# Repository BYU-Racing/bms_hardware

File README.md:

# BYU Racing 2027 BMS Project

This repo contains all relevant PCB files and explanations relating to the team's custom solution for a Battery Management System (BMS)

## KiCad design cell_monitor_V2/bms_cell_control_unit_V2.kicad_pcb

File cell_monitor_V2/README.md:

# BMS Cell Monitor V2 Files
This folder contains the KiCad project files for the BMS Cell Monitor V2.

PCB handoff from Rugby 11/10/2026 ☠️🌹⛓️

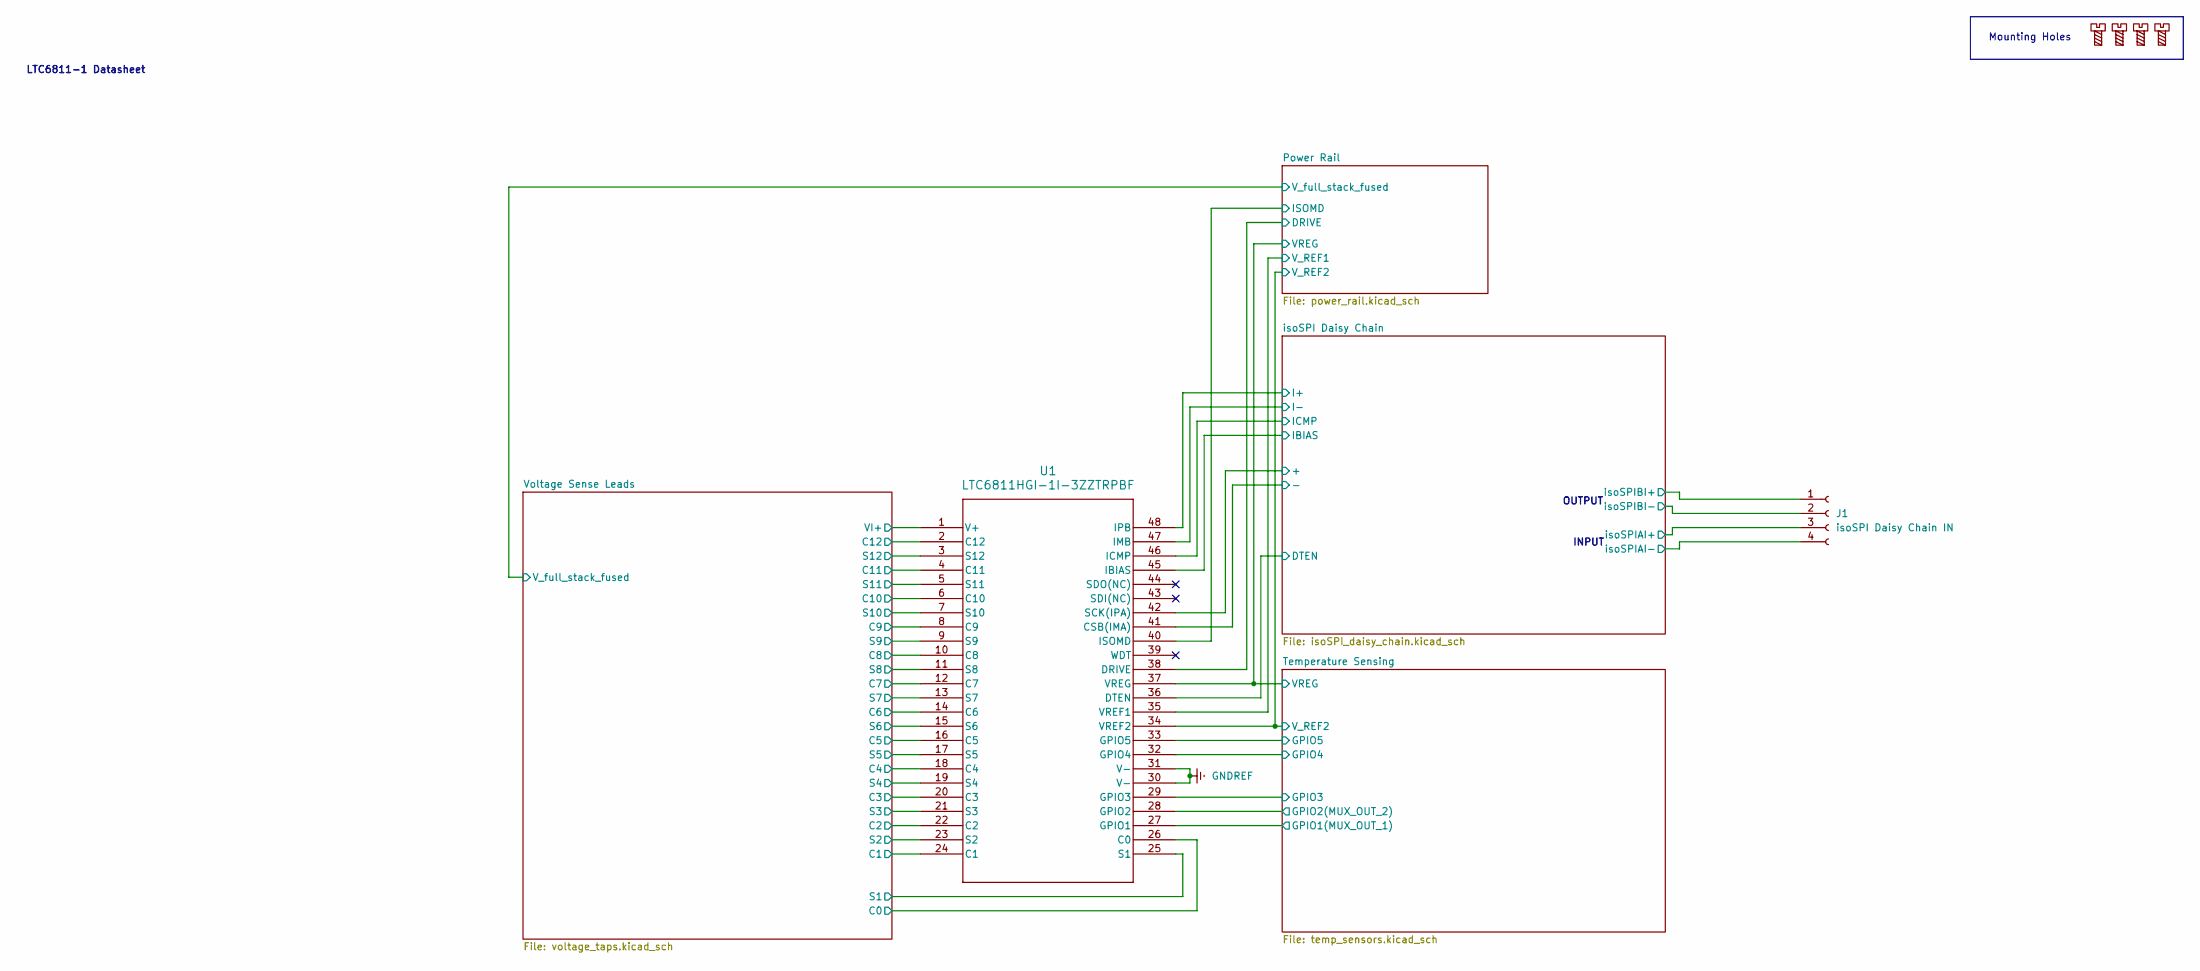
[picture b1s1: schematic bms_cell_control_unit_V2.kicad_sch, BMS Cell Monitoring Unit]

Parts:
H13, H14, H15, H16: MountingScrew; MountingHole_4mm
J1: isoSPI Daisy Chain IN; Molex_Micro-Fit_3.0_43650-0400_1x04_P3.00mm_Horizontal
U1: LTC6811HGI-1I-3ZZTRPBF; 05-08-1887_ADI

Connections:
/Power Rail/DRIVE: U1.38 (DRIVE); also elsewhere on the board
/Power Rail/VREG: U1.37 (VREG), U1.40 (ISOMD); also elsewhere on the board
/Power Rail/V_REF1: U1.35 (VREF1); also elsewhere on the board
/Power Rail/V_REF2: U1.34 (VREF2); also elsewhere on the board
/Temperature Sensing/GPIO1(MUX_OUT_1): U1.27 (GPIO1); also elsewhere on the board
/Temperature Sensing/GPIO2(MUX_OUT_2): U1.28 (GPIO2); also elsewhere on the board
/Temperature Sensing/GPIO3: U1.29 (GPIO3); also elsewhere on the board
/Temperature Sensing/GPIO4: U1.32 (GPIO4); also elsewhere on the board
/Temperature Sensing/GPIO5: U1.33 (GPIO5); also elsewhere on the board
/Voltage Sense Leads/C0: U1.26 (C0); also elsewhere on the board
/Voltage Sense Leads/C1: U1.24 (C1); also elsewhere on the board
/Voltage Sense Leads/C2: U1.22 (C2); also elsewhere on the board
/Voltage Sense Leads/C3: U1.20 (C3); also elsewhere on the board
/Voltage Sense Leads/C4: U1.18 (C4); also elsewhere on the board
/Voltage Sense Leads/C5: U1.16 (C5); also elsewhere on the board
/Voltage Sense Leads/C6: U1.14 (C6); also elsewhere on the board
/Voltage Sense Leads/C7: U1.12 (C7); also elsewhere on the board
/Voltage Sense Leads/C8: U1.10 (C8); also elsewhere on the board
/Voltage Sense Leads/C9: U1.8 (C9); also elsewhere on the board
/Voltage Sense Leads/C10: U1.6 (C10); also elsewhere on the board
/Voltage Sense Leads/C11: U1.4 (C11); also elsewhere on the board
/Voltage Sense Leads/C12: U1.2 (C12); also elsewhere on the board
/Voltage Sense Leads/S1: U1.25 (S1); also elsewhere on the board
/Voltage Sense Leads/S2: U1.23 (S2); also elsewhere on the board
/Voltage Sense Leads/S3: U1.21 (S3); also elsewhere on the board
/Voltage Sense Leads/S4: U1.19 (S4); also elsewhere on the board
/Voltage Sense Leads/S5: U1.17 (S5); also elsewhere on the board
/Voltage Sense Leads/S6: U1.15 (S6); also elsewhere on the board
/Voltage Sense Leads/S7: U1.13 (S7); also elsewhere on the board
/Voltage Sense Leads/S8: U1.11 (S8); also elsewhere on the board
/Voltage Sense Leads/S9: U1.9 (S9); also elsewhere on the board
/Voltage Sense Leads/S10: U1.7 (S10); also elsewhere on the board
/Voltage Sense Leads/S11: U1.5 (S11); also elsewhere on the board
/Voltage Sense Leads/S12: U1.3 (S12); also elsewhere on the board
/Voltage Sense Leads/VI+: U1.1 (V+); also elsewhere on the board
/isoSPI Daisy Chain/+: U1.42 (SCK(IPA)); also elsewhere on the board
/isoSPI Daisy Chain/-: U1.41 (CSB(IMA)); also elsewhere on the board
/isoSPI Daisy Chain/I+: U1.48 (IPB); also elsewhere on the board
/isoSPI Daisy Chain/I-: U1.47 (IMB); also elsewhere on the board
/isoSPI Daisy Chain/IBIAS: U1.45 (IBIAS); also elsewhere on the board
/isoSPI Daisy Chain/ICMP: U1.46 (ICMP); also elsewhere on the board
/isoSPI Daisy Chain/isoSPIAI+: J1.3; also elsewhere on the board
/isoSPI Daisy Chain/isoSPIAI-: J1.4; also elsewhere on the board
/isoSPI Daisy Chain/isoSPIBI+: J1.1; also elsewhere on the board
/isoSPI Daisy Chain/isoSPIBI-: J1.2; also elsewhere on the board
GNDREF: U1.30 (V-), U1.31 (V-), U1.36 (DTEN); also elsewhere on the board

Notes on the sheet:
OUTPUT
INPUT
LTC6811-1 Datasheet
Mounting Holes

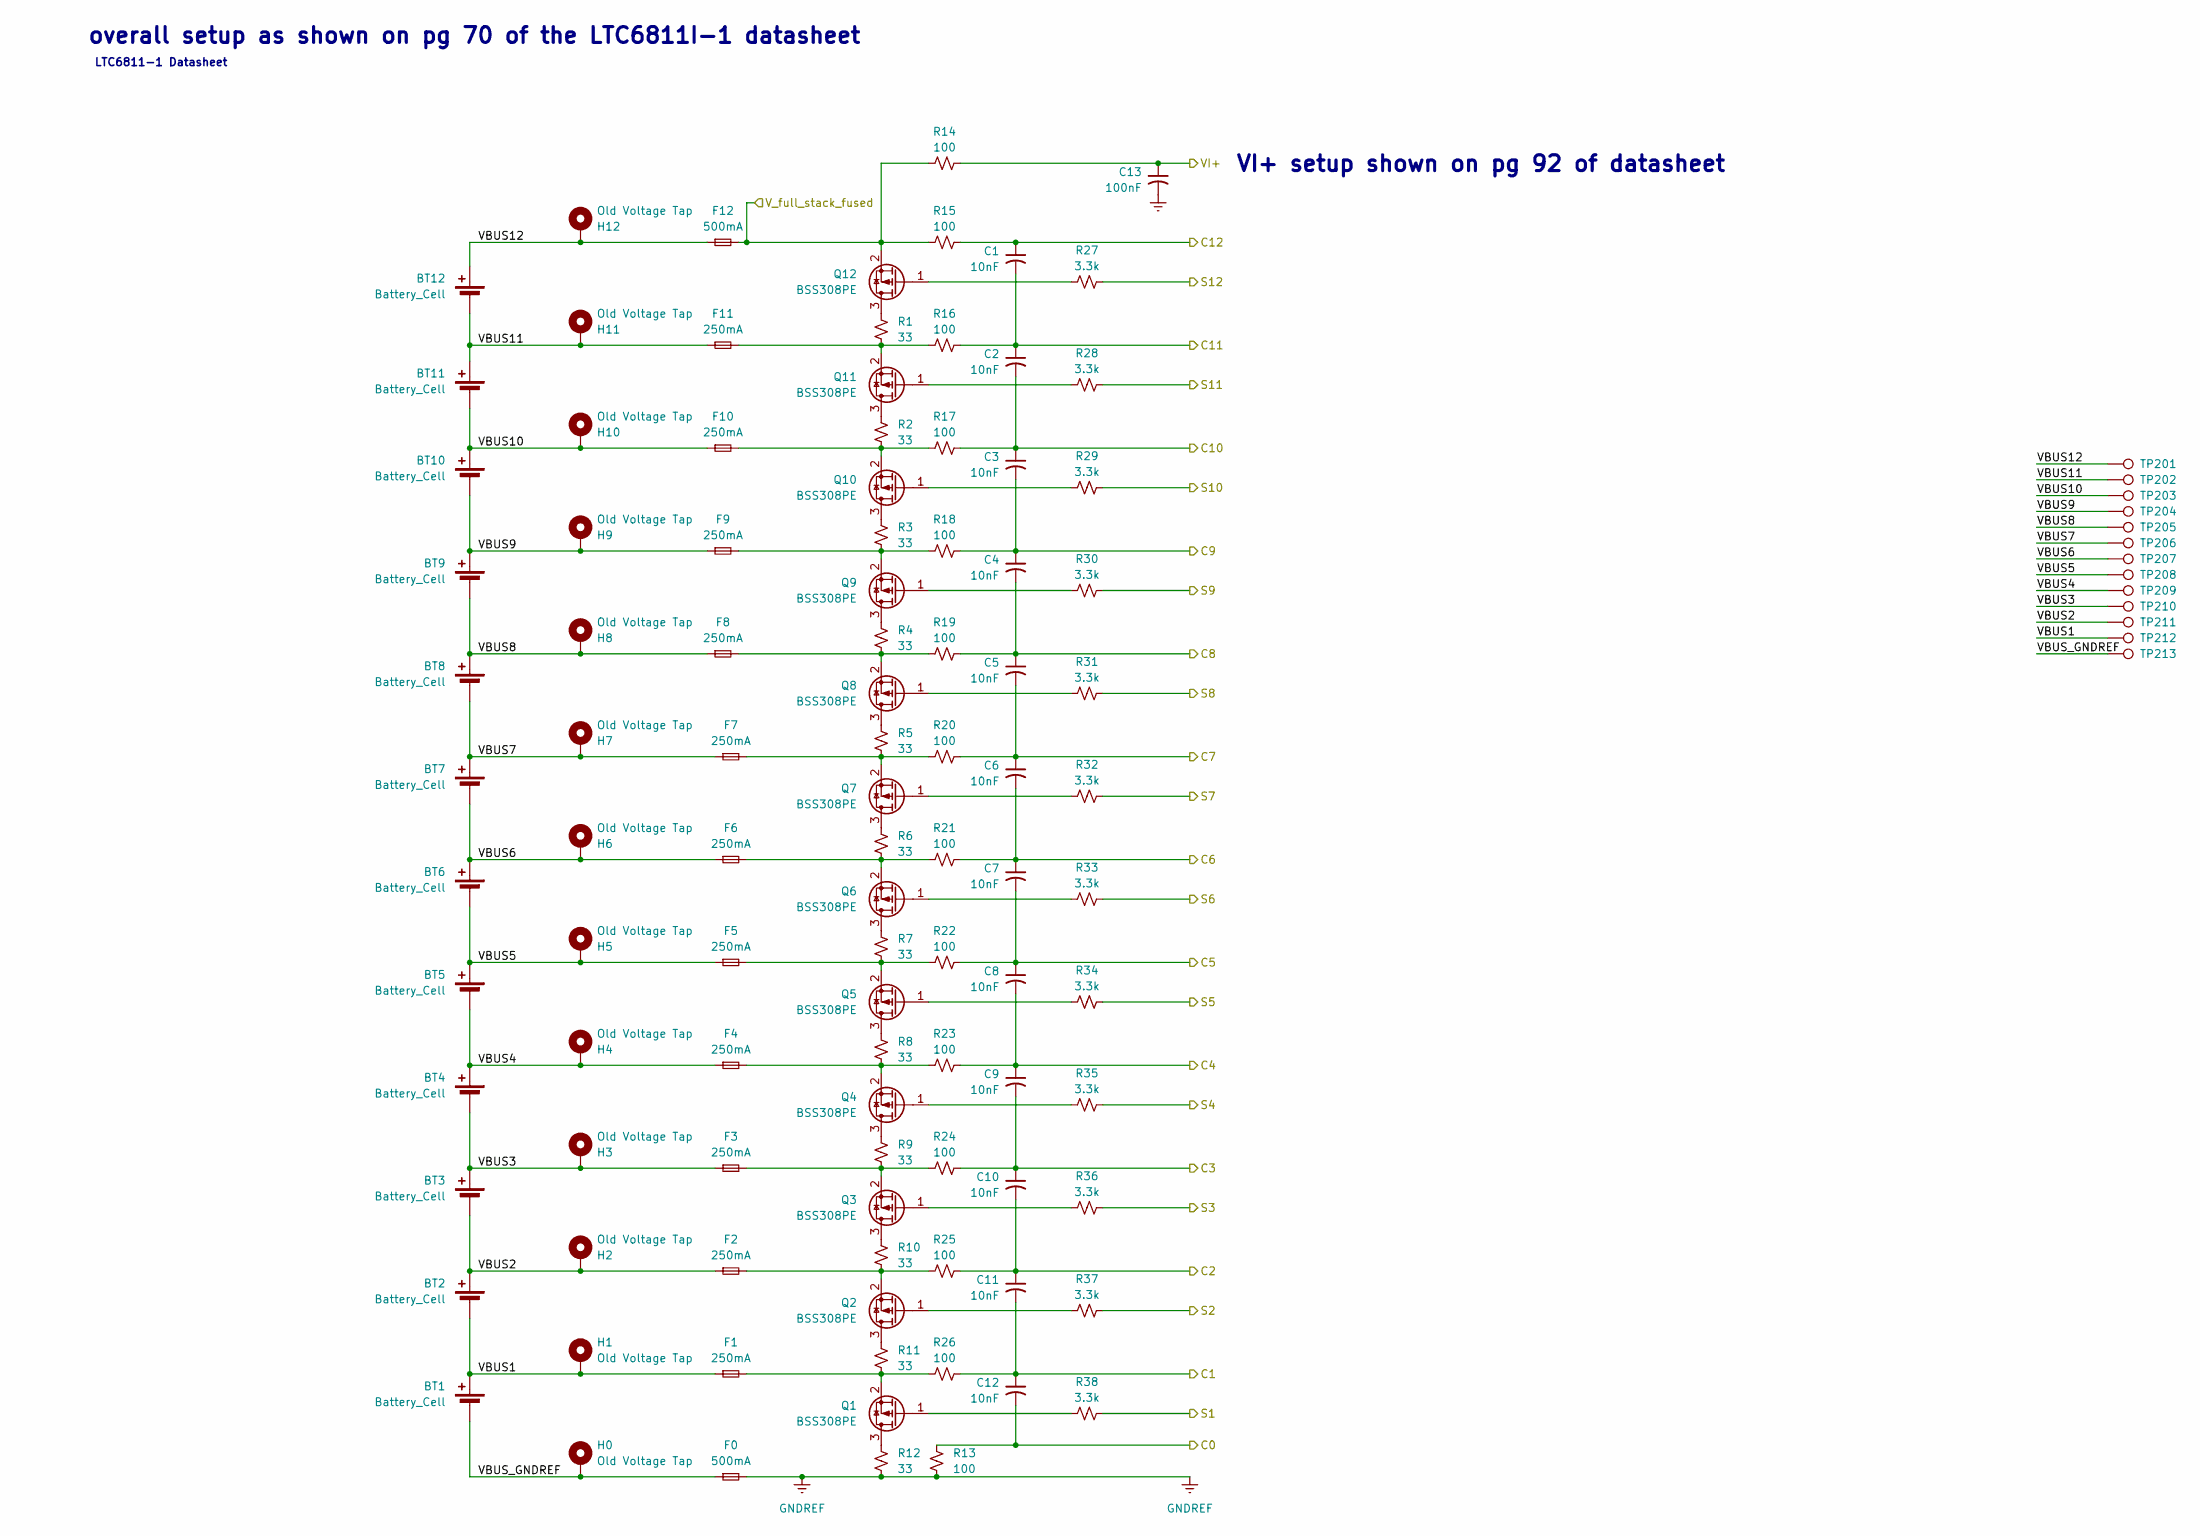
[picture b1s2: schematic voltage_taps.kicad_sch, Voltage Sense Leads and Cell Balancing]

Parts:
BT1, BT2, BT3, BT4, BT5, BT6, BT7, BT8, BT9, BT10, BT11, BT12: Battery_Cell
C1, C2, C3, C4, C5, C6, C7, C8, C9, C10, C11, C12: 10nF; C_0603_1608Metric_Pad1.08x0.95mm_HandSolder
C13: 100nF; C_0805_2012Metric_Pad1.18x1.45mm_HandSolder
F0, F12: 500mA; Littelfuse_01550900M_Fuse_Blok_Cartridge
F1, F2, F3, F4, F5, F6, F7, F8, F9, F10, F11: 250mA; Littelfuse_01550900M_Fuse_Blok_Cartridge
H0, H1, H2, H3, H4, H5, H6, H7, H8, H9, H10, H11, H12: Old Voltage Tap; Votage_taps
Q1, Q2, Q3, Q4, Q5, Q6, Q7, Q8, Q9, Q10, Q11, Q12: BSS308PE; SOT-23_Handsoldering
R1, R2, R3, R4, R5, R6, R7, R8, R9, R10, R11, R12: 33; Balance_Resistor_Thermal_Pad_Updated
R13, R14, R15, R16, R17, R18, R19, R20, R21, R22, R23, R24, R25, R26: 100; R_0603_1608Metric_Pad0.98x0.95mm_HandSolder
R27, R28, R29, R30, R31, R32, R33, R34, R35, R36, R37, R38: 3.3k; R_0603_1608Metric_Pad0.98x0.95mm_HandSolder
TP201, TP202, TP203, TP204, TP205, TP206, TP207, TP208, TP209, TP210, TP211, TP212, TP213: TestPoint; TestPoint_Pad_D2.0mm

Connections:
/Power Rail/V_full_stack_fused: F12.2, Q12.2 (S), R14.2, R15.2; also elsewhere on the board
/Voltage Sense Leads/C0: C12.2, R13.1; also elsewhere on the board
/Voltage Sense Leads/C1: C11.2, C12.1, R26.1; also elsewhere on the board
/Voltage Sense Leads/C2: C10.2, C11.1, R25.1; also elsewhere on the board
/Voltage Sense Leads/C3: C9.2, C10.1, R24.1; also elsewhere on the board
/Voltage Sense Leads/C4: C8.2, C9.1, R23.1; also elsewhere on the board
/Voltage Sense Leads/C5: C7.2, C8.1, R22.1; also elsewhere on the board
/Voltage Sense Leads/C6: C6.2, C7.1, R21.1; also elsewhere on the board
/Voltage Sense Leads/C7: C5.2, C6.1, R20.1; also elsewhere on the board
/Voltage Sense Leads/C8: C4.2, C5.1, R19.1; also elsewhere on the board
/Voltage Sense Leads/C9: C3.2, C4.1, R18.1; also elsewhere on the board
/Voltage Sense Leads/C10: C2.2, C3.1, R17.1; also elsewhere on the board
/Voltage Sense Leads/C11: C1.2, C2.1, R16.1; also elsewhere on the board
/Voltage Sense Leads/C12: C1.1, R15.1; also elsewhere on the board
/Voltage Sense Leads/S1: R38.1; also elsewhere on the board
/Voltage Sense Leads/S2: R37.1; also elsewhere on the board
/Voltage Sense Leads/S3: R36.1; also elsewhere on the board
/Voltage Sense Leads/S4: R35.1; also elsewhere on the board
/Voltage Sense Leads/S5: R34.1; also elsewhere on the board
/Voltage Sense Leads/S6: R33.1; also elsewhere on the board
/Voltage Sense Leads/S7: R32.1; also elsewhere on the board
/Voltage Sense Leads/S8: R31.1; also elsewhere on the board
/Voltage Sense Leads/S9: R30.1; also elsewhere on the board
/Voltage Sense Leads/S10: R29.1; also elsewhere on the board
/Voltage Sense Leads/S11: R28.1; also elsewhere on the board
/Voltage Sense Leads/S12: R27.1; also elsewhere on the board
/Voltage Sense Leads/VBUS1: BT1.1 (+), BT2.2 (-), F1.1, H1.1 (1_1), TP212.1 (1_1)
/Voltage Sense Leads/VBUS2: BT2.1 (+), BT3.2 (-), F2.1, H2.1 (1_1), TP211.1 (1_1)
/Voltage Sense Leads/VBUS3: BT3.1 (+), BT4.2 (-), F3.1, H3.1 (1_1), TP210.1 (1_1)
/Voltage Sense Leads/VBUS4: BT4.1 (+), BT5.2 (-), F4.1, H4.1 (1_1), TP209.1 (1_1)
/Voltage Sense Leads/VBUS5: BT5.1 (+), BT6.2 (-), F5.1, H5.1 (1_1), TP208.1 (1_1)
/Voltage Sense Leads/VBUS6: BT6.1 (+), BT7.2 (-), F6.1, H6.1 (1_1), TP207.1 (1_1)
/Voltage Sense Leads/VBUS7: BT7.1 (+), BT8.2 (-), F7.1, H7.1 (1_1), TP206.1 (1_1)
/Voltage Sense Leads/VBUS8: BT8.1 (+), BT9.2 (-), F8.1, H8.1 (1_1), TP205.1 (1_1)
/Voltage Sense Leads/VBUS9: BT9.1 (+), BT10.2 (-), F9.1, H9.1 (1_1), TP204.1 (1_1)
/Voltage Sense Leads/VBUS10: BT10.1 (+), BT11.2 (-), F10.1, H10.1 (1_1), TP203.1 (1_1)
/Voltage Sense Leads/VBUS11: BT11.1 (+), BT12.2 (-), F11.1, H11.1 (1_1), TP202.1 (1_1)
/Voltage Sense Leads/VBUS12: BT12.1 (+), F12.1, H12.1 (1_1), TP201.1 (1_1)
/Voltage Sense Leads/VBUS_GNDREF: BT1.2 (-), F0.1, H0.1 (1_1), TP213.1 (1_1)
/Voltage Sense Leads/VI+: C13.1, R14.1; also elsewhere on the board
GNDREF: C13.2, F0.2, R12.2, R13.2; also elsewhere on the board
unnamed: Q1.3 (D), R12.1
unnamed: Q1.1 (G), R38.2
unnamed: F1.2, Q1.2 (S), R11.2, R26.2
unnamed: Q2.3 (D), R11.1
unnamed: Q2.1 (G), R37.2
unnamed: F2.2, Q2.2 (S), R10.2, R25.2
unnamed: Q3.3 (D), R10.1
unnamed: Q3.1 (G), R36.2
unnamed: F3.2, Q3.2 (S), R9.2, R24.2
unnamed: Q4.3 (D), R9.1
unnamed: Q4.1 (G), R35.2
unnamed: F4.2, Q4.2 (S), R8.2, R23.2
unnamed: Q5.3 (D), R8.1
unnamed: Q5.1 (G), R34.2
unnamed: F5.2, Q5.2 (S), R7.2, R22.2
unnamed: Q6.3 (D), R7.1
unnamed: Q6.1 (G), R33.2
unnamed: F6.2, Q6.2 (S), R6.2, R21.2
unnamed: Q7.3 (D), R6.1
unnamed: Q7.1 (G), R32.2
unnamed: F7.2, Q7.2 (S), R5.2, R20.2
unnamed: Q8.3 (D), R5.1
unnamed: Q8.1 (G), R31.2
unnamed: F8.2, Q8.2 (S), R4.2, R19.2
unnamed: Q9.3 (D), R4.1
unnamed: Q9.1 (G), R30.2
unnamed: F9.2, Q9.2 (S), R3.2, R18.2
unnamed: Q10.3 (D), R3.1
unnamed: Q10.1 (G), R29.2
unnamed: F10.2, Q10.2 (S), R2.2, R17.2
unnamed: Q11.3 (D), R2.1
unnamed: Q11.1 (G), R28.2
unnamed: F11.2, Q11.2 (S), R1.2, R16.2
unnamed: Q12.3 (D), R1.1
unnamed: Q12.1 (G), R27.2

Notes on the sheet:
LTC6811-1 Datasheet
VI+ setup shown on pg 92 of datasheet
overall setup as shown on pg 70 of the LTC6811I-1 datasheet

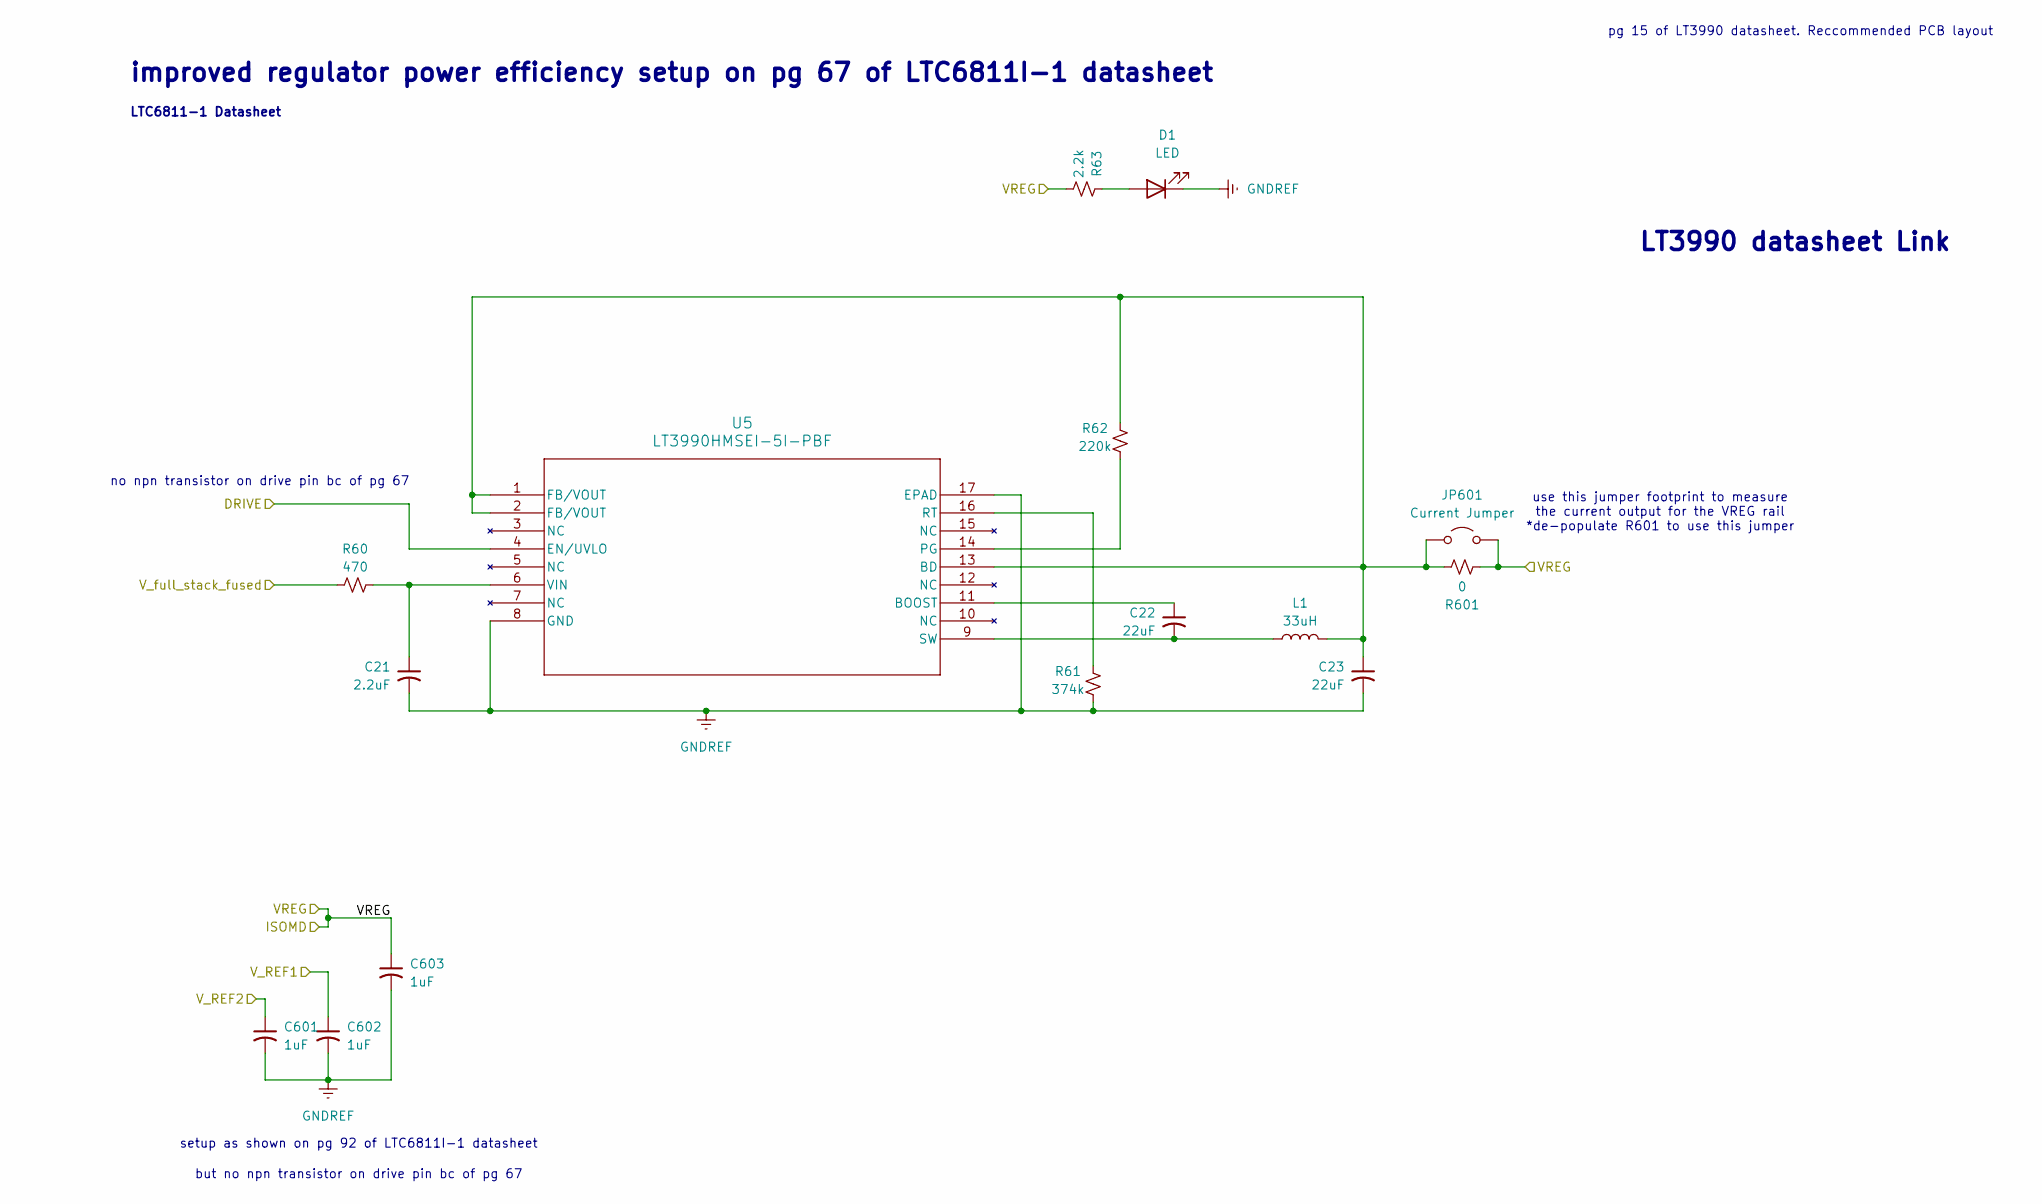
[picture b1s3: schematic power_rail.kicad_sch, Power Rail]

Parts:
C21: 2.2uF; C_1210_3225Metric_Pad1.33x2.70mm_HandSolder; DigiKey_Part_Number AC1210KKX7R0BB225
C22, C23: 22uF; C_0805_2012Metric_Pad1.18x1.45mm_HandSolder
C601, C602, C603: 1uF; C_0805_2012Metric_Pad1.18x1.45mm_HandSolder
D1: LED; R_0805_2012Metric_Pad1.20x1.40mm_HandSolder
JP601: Current Jumper; PinHeader_1x02_P2.54mm_Vertical
L1: 33uH; IND_LQH5BPH330MT0L; DigiKey_Part_Number LQH5BPH330MT0L
R60: 470; R_0805_2012Metric_Pad1.20x1.40mm_HandSolder
R61: 374k; R_0603_1608Metric_Pad0.98x0.95mm_HandSolder
R62: 220k; R_0603_1608Metric_Pad0.98x0.95mm_HandSolder
R63: 2.2k; R_0603_1608Metric_Pad0.98x0.95mm_HandSolder
R601: 0; R_0603_1608Metric_Pad0.98x0.95mm_HandSolder
U5: LT3990HMSEI-5I-PBF; MSOP-16-1EP_3x4.039mm_P0.5mm_EP1.651x2.845mm_ThermalVias

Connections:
/Power Rail/DRIVE: U5.4 (EN/UVLO); also elsewhere on the board
/Power Rail/VREG: C603.1, JP601.2 (B), R63.2, R601.2; also elsewhere on the board
/Power Rail/V_REF1: C602.1; also elsewhere on the board
/Power Rail/V_REF2: C601.1; also elsewhere on the board
/Power Rail/V_full_stack_fused: R60.2; also elsewhere on the board
GNDREF: C21.2, C23.2, C601.2, C602.2, C603.2, D1.1 (K), R61.2, U5.8 (GND), U5.17 (EPAD); also elsewhere on the board
unnamed: D1.2 (A), R63.1
unnamed: C23.1, JP601.1 (A), L1.2, R62.1, R601.1, U5.1 (FB/VOUT), U5.2 (FB/VOUT), U5.13 (BD)
unnamed: C22.1, U5.11 (BOOST)
unnamed: R62.2, U5.14 (PG)
unnamed: R61.1, U5.16 (RT)
unnamed: C22.2, L1.1, U5.9 (SW)
unnamed: C21.1, R60.1, U5.6 (VIN)

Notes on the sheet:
setup as shown on pg 92 of LTC6811I-1 datasheet
no npn transistor on drive pin bc of pg 67
LTC6811-1 Datasheet
pg 15 of LT3990 datasheet. Reccommended PCB layout
improved regulator power efficiency setup on pg 67 of LTC6811I-1 datasheet
but no npn transistor on drive pin bc of pg 67
LT3990 datasheet Link
use this jumper footprint to measure the current output for the VREG rail *de-populate R601 to use this jumper

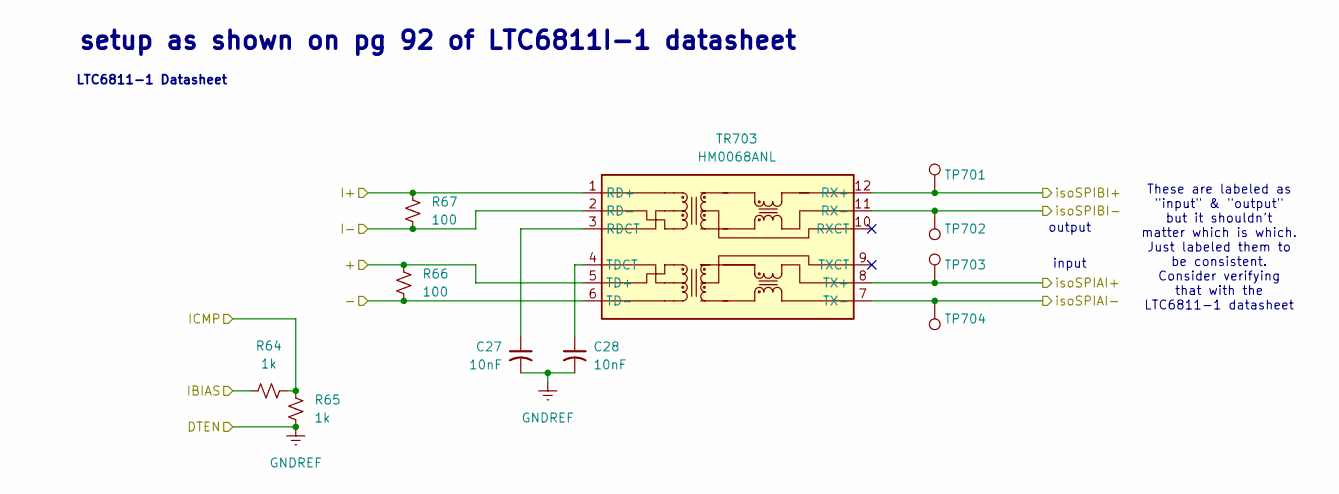
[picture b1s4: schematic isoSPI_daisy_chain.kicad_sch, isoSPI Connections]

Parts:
C27, C28: 10nF; C_0805_2012Metric_Pad1.18x1.45mm_HandSolder
R64, R65: 1k; R_0603_1608Metric_Pad0.98x0.95mm_HandSolder
R66, R67: 100; R_0805_2012Metric_Pad1.20x1.40mm_HandSolder
TP701, TP702, TP703, TP704: TestPoint; TestPoint_Pad_D2.0mm
TR703: HM0068ANL; Pulse_HM0068ANL

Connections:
/isoSPI Daisy Chain/+: R66.2, TR703.5 (TD+); also elsewhere on the board
/isoSPI Daisy Chain/-: R66.1, TR703.6 (TD-); also elsewhere on the board
/isoSPI Daisy Chain/I+: R67.2, TR703.1 (RD+); also elsewhere on the board
/isoSPI Daisy Chain/I-: R67.1, TR703.2 (RD-); also elsewhere on the board
/isoSPI Daisy Chain/IBIAS: R64.2; also elsewhere on the board
/isoSPI Daisy Chain/ICMP: R64.1, R65.2; also elsewhere on the board
/isoSPI Daisy Chain/isoSPIAI+: TP703.1 (1_1), TR703.8 (TX+); also elsewhere on the board
/isoSPI Daisy Chain/isoSPIAI-: TP704.1 (1_1), TR703.7 (TX-); also elsewhere on the board
/isoSPI Daisy Chain/isoSPIBI+: TP701.1 (1_1), TR703.12 (RX+); also elsewhere on the board
/isoSPI Daisy Chain/isoSPIBI-: TP702.1 (1_1), TR703.11 (RX-); also elsewhere on the board
GNDREF: C27.2, C28.2, R65.1; also elsewhere on the board
unnamed: C27.1, TR703.3 (RDCT)
unnamed: C28.1, TR703.4 (TDCT)

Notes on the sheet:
output
These are labeled as "input" & "output" but it shouldn't matter which is which. Just labeled them to be consistent. Consider verifying that with the LTC6811-1 datasheet
setup as shown on pg 92 of LTC6811I-1 datasheet
LTC6811-1 Datasheet
input

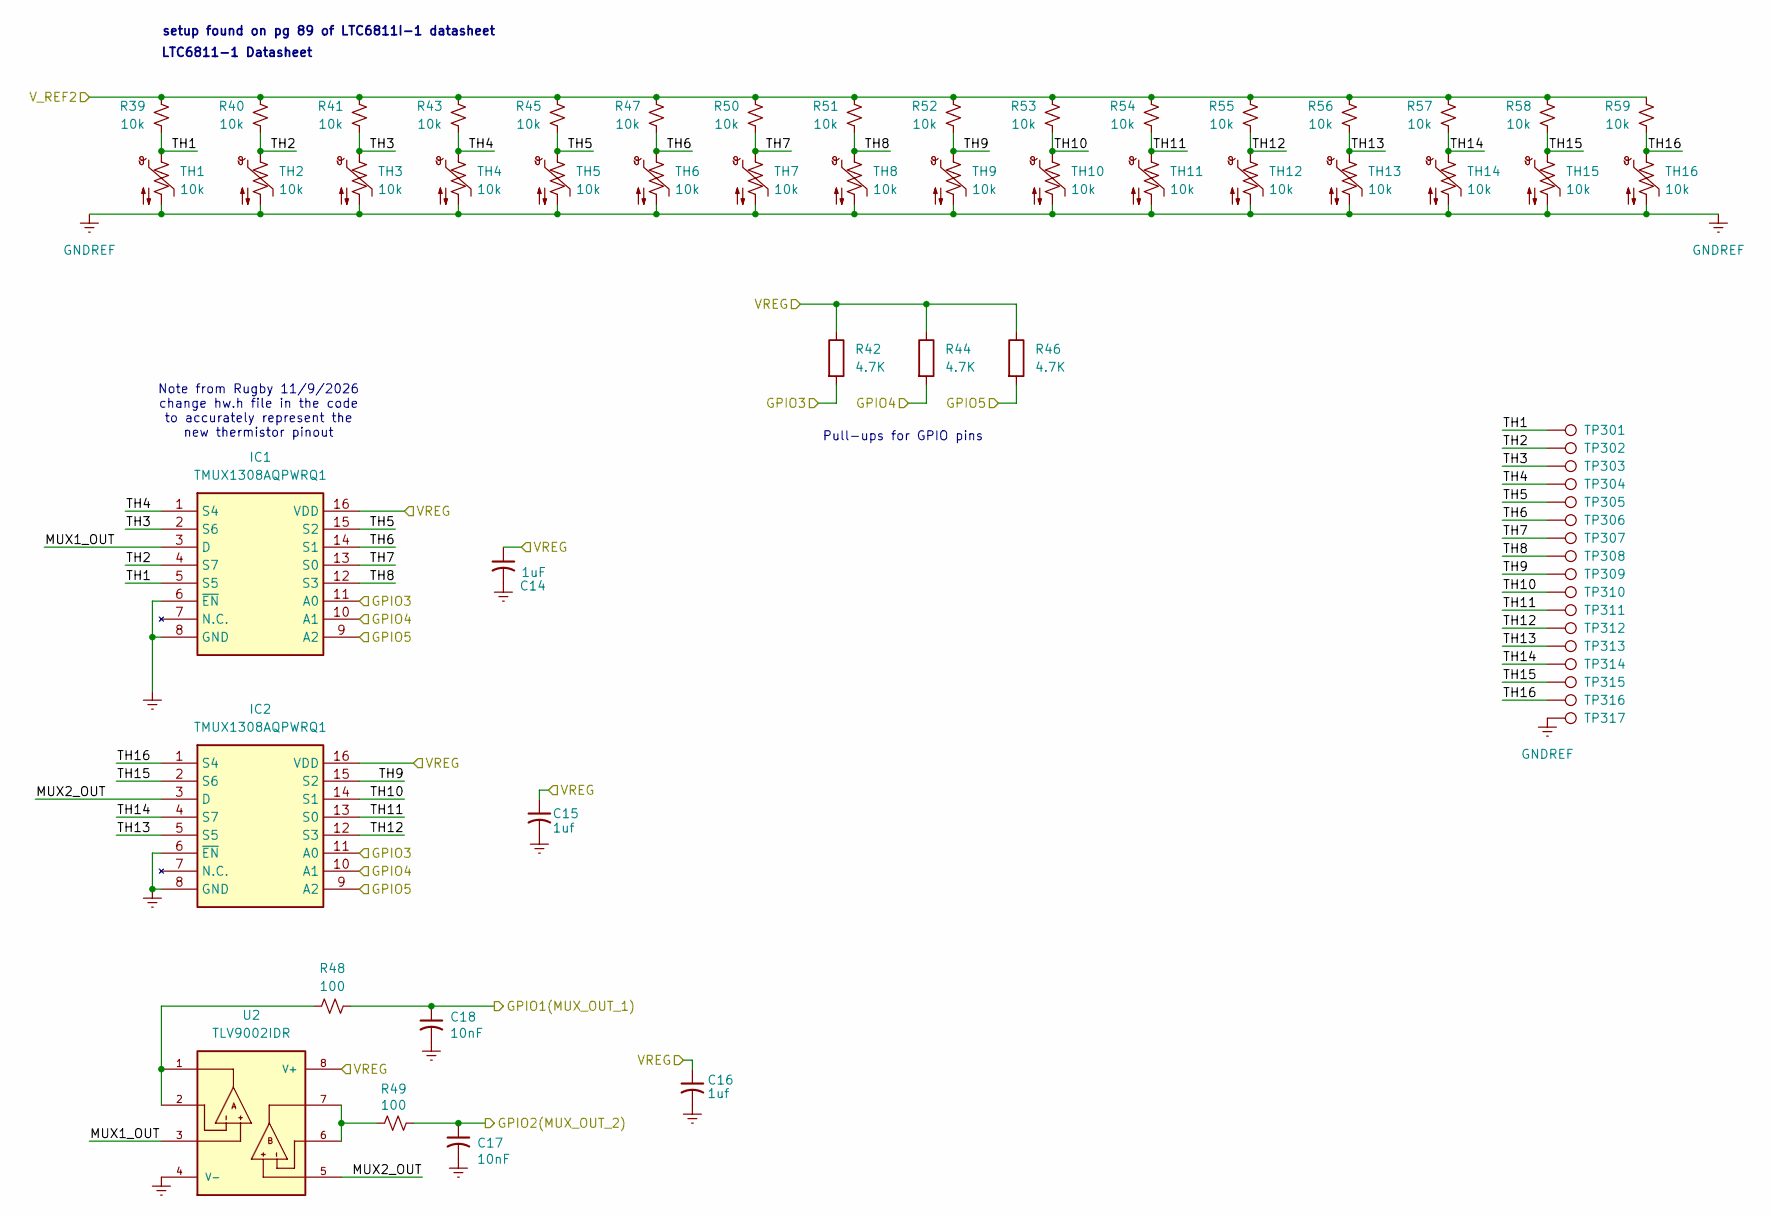
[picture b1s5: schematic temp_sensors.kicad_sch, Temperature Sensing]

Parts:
C14: 1uF; R_0805_2012Metric_Pad1.20x1.40mm_HandSolder
C15, C16: 1uf; R_0805_2012Metric_Pad1.20x1.40mm_HandSolder
C17, C18: 10nF; R_0805_2012Metric_Pad1.20x1.40mm_HandSolder
IC1, IC2: TMUX1308AQPWRQ1; SOP65P640X120-16N; Manufacturer_Part_Number TMUX1308AQPWRQ1; Mouser Part Number 595-TMUX1308AQPWRQ1
R39, R40, R41, R43, R45, R47, R50, R51, R52, R53, R54, R55, R56, R57, R58, R59: 10k; R_0603_1608Metric_Pad0.98x0.95mm_HandSolder
R42, R44, R46: 4.7K; R_0603_1608Metric_Pad0.98x0.95mm_HandSolder
R48, R49: 100; R_0603_1608Metric_Pad0.98x0.95mm_HandSolder
TH1, TH2, TH3, TH4, TH5, TH6, TH7, TH8, TH9, TH10, TH11, TH12, TH13, TH14, TH15, TH16: 10k; Thermistor_Pad
TP301, TP302, TP303, TP304, TP305, TP306, TP307, TP308, TP309, TP310, TP311, TP312, TP313, TP314, TP315, TP316, TP317: TestPoint; TestPoint_Pad_D2.0mm
U2: TLV9002IDR; SOIC-8_3.9x4.9mm_P1.27mm; PARTREV O

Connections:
/Power Rail/VREG: C14.1, C15.1, C16.1, IC1.16 (VDD), IC2.16 (VDD), R42.1, R44.1, R46.1, U2.8 (V+); also elsewhere on the board
/Power Rail/V_REF2: R39.1, R40.1, R41.1, R43.1, R45.1, R47.1, R50.1, R51.1, R52.1, R53.1, R54.1, R55.1, R56.1, R57.1, R58.1, R59.1; also elsewhere on the board
/Temperature Sensing/GPIO1(MUX_OUT_1): C18.1, R48.1; also elsewhere on the board
/Temperature Sensing/GPIO2(MUX_OUT_2): C17.1, R49.1; also elsewhere on the board
/Temperature Sensing/GPIO3: IC1.11 (A0), IC2.11 (A0), R42.2; also elsewhere on the board
/Temperature Sensing/GPIO4: IC1.10 (A1), IC2.10 (A1), R44.2; also elsewhere on the board
/Temperature Sensing/GPIO5: IC1.9 (A2), IC2.9 (A2), R46.2; also elsewhere on the board
/Temperature Sensing/MUX1_OUT: IC1.3 (D), U2.3
/Temperature Sensing/MUX2_OUT: IC2.3 (D), U2.5
/Temperature Sensing/TH1: IC1.5 (S5), R39.2, TH1.1, TP301.1 (1_1)
/Temperature Sensing/TH2: IC1.4 (S7), R40.2, TH2.1, TP302.1 (1_1)
/Temperature Sensing/TH3: IC1.2 (S6), R41.2, TH3.1, TP303.1 (1_1)
/Temperature Sensing/TH4: IC1.1 (S4), R43.2, TH4.1, TP304.1 (1_1)
/Temperature Sensing/TH5: IC1.15 (S2), R45.2, TH5.1, TP305.1 (1_1)
/Temperature Sensing/TH6: IC1.14 (S1), R47.2, TH6.1, TP306.1 (1_1)
/Temperature Sensing/TH7: IC1.13 (S0), R50.2, TH7.1, TP307.1 (1_1)
/Temperature Sensing/TH8: IC1.12 (S3), R51.2, TH8.1, TP308.1 (1_1)
/Temperature Sensing/TH9: IC2.15 (S2), R52.2, TH9.1, TP309.1 (1_1)
/Temperature Sensing/TH10: IC2.14 (S1), R53.2, TH10.1, TP310.1 (1_1)
/Temperature Sensing/TH11: IC2.13 (S0), R54.2, TH11.1, TP311.1 (1_1)
/Temperature Sensing/TH12: IC2.12 (S3), R55.2, TH12.1, TP312.1 (1_1)
/Temperature Sensing/TH13: IC2.5 (S5), R56.2, TH13.1, TP313.1 (1_1)
/Temperature Sensing/TH14: IC2.4 (S7), R57.2, TH14.1, TP314.1 (1_1)
/Temperature Sensing/TH15: IC2.2 (S6), R58.2, TH15.1, TP315.1 (1_1)
/Temperature Sensing/TH16: IC2.1 (S4), R59.2, TH16.1, TP316.1 (1_1)
GNDREF: C14.2, C15.2, C16.2, C17.2, C18.2, IC1.6 (~EN), IC1.8 (GND), IC2.6 (~EN), IC2.8 (GND), TH1.2, TH2.2, TH3.2, TH4.2, TH5.2, TH6.2, TH7.2, TH8.2, TH9.2, TH10.2, TH11.2, TH12.2, TH13.2, TH14.2, TH15.2, TH16.2, TP317.1 (1_1), U2.4 (V-); also elsewhere on the board
unnamed: R48.2, U2.1, U2.2
unnamed: R49.2, U2.6, U2.7

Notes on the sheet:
Pull-ups for GPIO pins
Note from Rugby 11/9/2026 change hw.h file in the code to accurately represent the new thermistor pinout
LTC6811-1 Datasheet
setup found on pg 89 of LTC6811I-1 datasheet

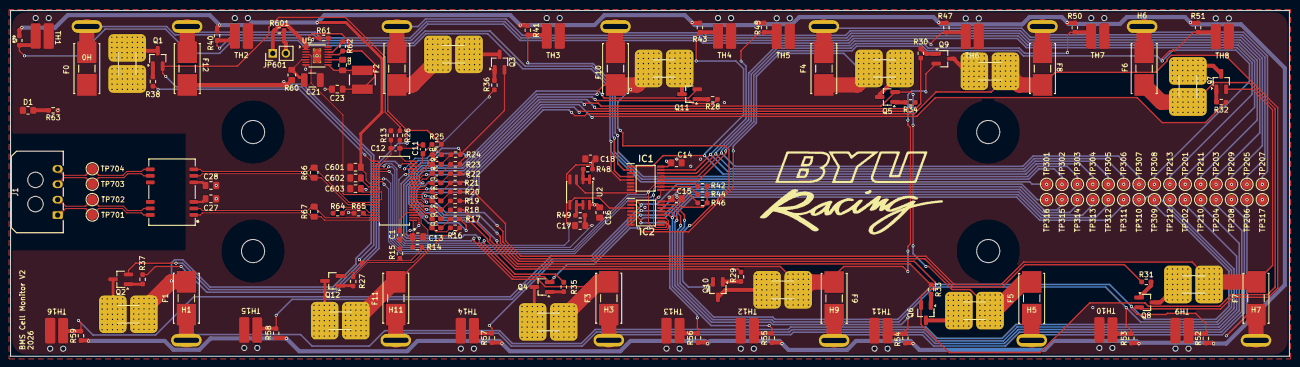
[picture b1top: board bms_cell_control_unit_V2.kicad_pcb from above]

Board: 4 copper layers, 249.0 x 67.3 mm, 200 parts (0 on the bottom side), 124 nets.

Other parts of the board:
H14#2, H14#3, H14#4, H14#5: MountingScrew; MountingHole_4mm
